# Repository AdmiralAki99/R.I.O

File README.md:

# Smartwatch Software

## Overview

A basic smartwatch software that is used for personal use and understanding how to read schematics, design PCB, understand embedded sytems.

## Render

https://github.com/user-attachments/assets/5ccf8013-91de-4bed-8570-e81a325c24fe

## Schematic

## Features

<ul>
    <li> BLE Communication With Swift Companion App</li>
    <li> Fits Inside 42mm Metal Watch Case </li>
</ul>

## Hardware Used
<ol>
    <li> ESP32 S3 MCU </li>
    <li> GC9A01 TFT Screen 1.28 Touch Screen </li>
    <li> Resistor (160k)</li>
    <li> Resistor (442k)</li>
    <li> 4 pin Magnetic Connector</li>
    <li> JST 2 Pin Connector RA</li>
    <li> Two Vertical Tactile Switch</li>
    <li>Schotky Diode </li>
</ol>

## Challenges Faced

<ul>
    <li> Understanding Schematics to connect the data pins and power pins to the magnetic connector to allow for flashing of the board </li>
    <li> Implementing BLE GATT Server & Characteristics</li>
    <li> Controlling power consumption to increase battery life </li>
    <li> Designing 3D housing for the watch to be placed inside the metal watch</li>
    <li> Designing PCB board using KiCad</li>
</ul>

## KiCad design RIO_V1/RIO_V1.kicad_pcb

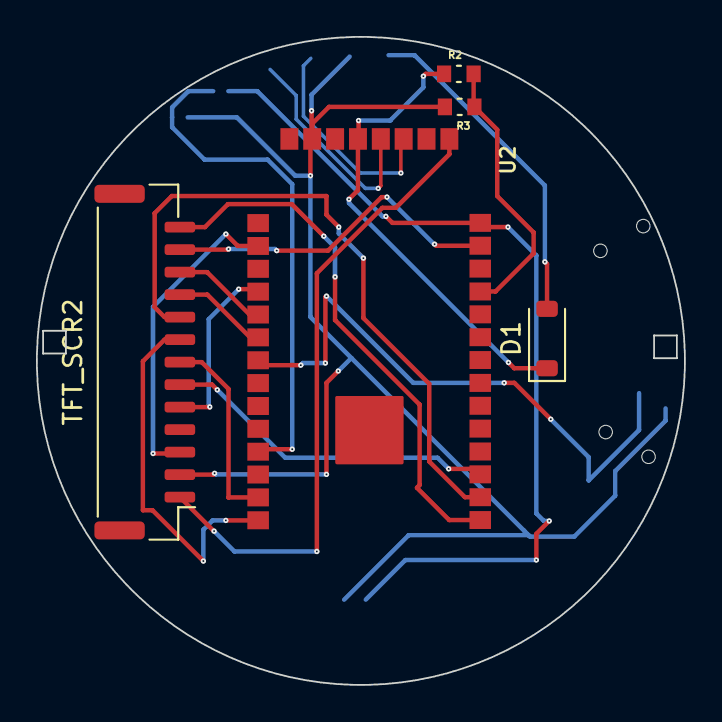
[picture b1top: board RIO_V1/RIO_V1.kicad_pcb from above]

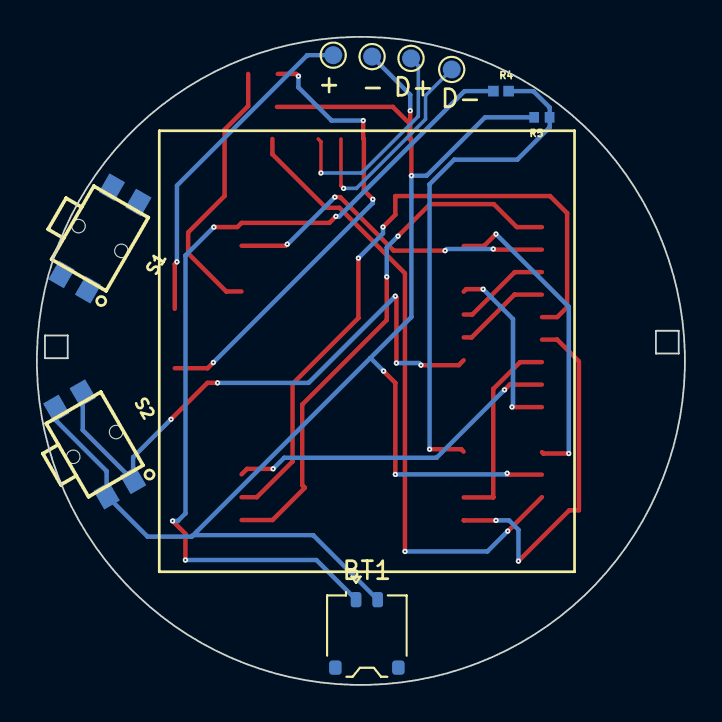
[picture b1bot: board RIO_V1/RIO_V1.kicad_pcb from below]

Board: 2 copper layers, 36.0 x 36.0 mm, 14 parts (9 on the bottom side), 22 nets.

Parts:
+: TestPoint; TestPoint_Pad_D1.0mm
-: TestPoint; TestPoint_Pad_D1.0mm
BT1: Battery; JST_ACH_BM02B-ACHSS-GAN-ETF_1x02-1MP_P1.20mm_Vertical
D1: MBR0530-TP; D_SOD-123
D+: TestPoint; TestPoint_Pad_D1.0mm
D-: TestPoint; TestPoint_Pad_D1.0mm
R2, R3: 50k; RESC1608X55N
R4: 442k; RESC1005X35N
R5: 160k; RESC1005X40N
S1, S2: TL1014BF160QG
TFT_SCR2: GH_CONNECTOR; JST_GH_BM13B-GHS-TBT_1x13-1MP_P1.25mm_Vertical
U2: NanoS3

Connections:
+3V3: TFT_SCR2.1, U2.8 (3v3)
+5V: D1.1 (K), R2.1, U2.4 (5V)
D+: D+.1, U2.6 (D+)
D-: D-.1, U2.5 (D-)
GND: -.1, BT1.2 (-), R3.2, R5.2, S1.1, S1.3, S2.2, S2.4, TFT_SCR2.2, U2.2 (GND)
IO0: S2.1, S2.3, U2.29 (IO0)
IO1: R4.2, R5.1, U2.33 (IO1)
IO3: TFT_SCR2.7, U2.35 (IO3)
IO4: TFT_SCR2.8, U2.36 (IO4)
IO5: TFT_SCR2.13, U2.22 (IO5)
IO6: TFT_SCR2.9, U2.21 (IO6)
IO7: TFT_SCR2.6, U2.20 (IO7)
IO8: TFT_SCR2.10, U2.28 (IO8)
IO9: TFT_SCR2.11, U2.27 (IO9)
IO17: R2.2, R3.1, U2.12 (IO17)
IO21: TFT_SCR2.12, U2.10 (IO21)
IO34: TFT_SCR2.5, U2.26 (IO34)
IO35: TFT_SCR2.4, U2.23 (IO35)
IO37: TFT_SCR2.3, U2.24 (IO37)
unnamed: +.1, D1.2 (A)
RESET: S1.2, S1.4, U2.3 (RESET)
VBAT: BT1.1 (+), R4.1, U2.9 (VBAT)

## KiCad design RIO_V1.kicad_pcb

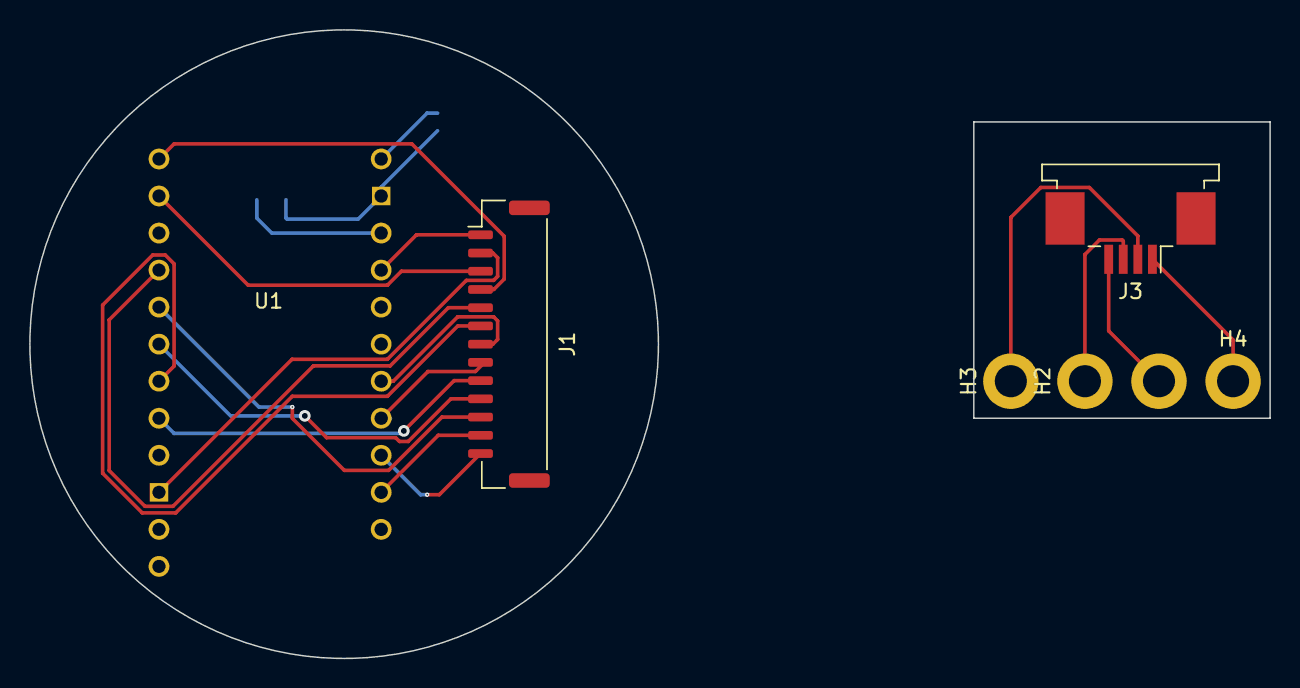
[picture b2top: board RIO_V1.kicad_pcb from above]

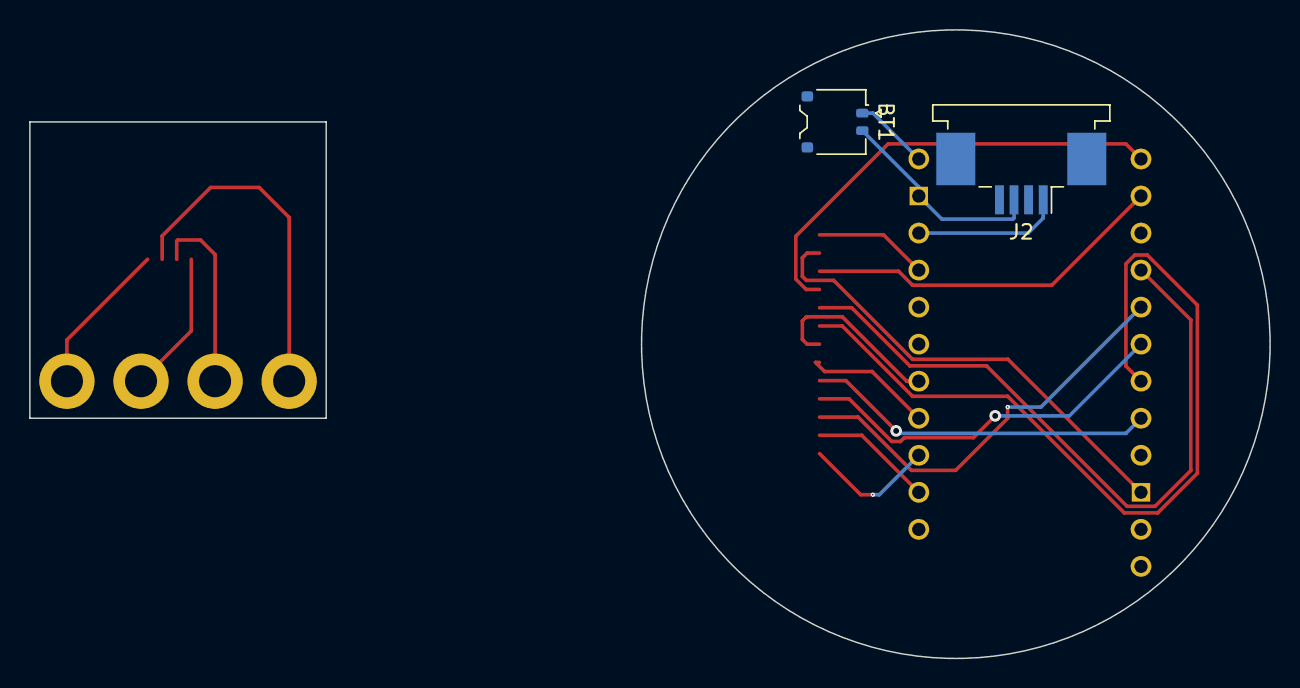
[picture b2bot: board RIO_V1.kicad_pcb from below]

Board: 2 copper layers, 85.1 x 43.1 mm, 9 parts (2 on the bottom side), 20 nets.

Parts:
BT1: Battery; JST_ACH_BM02B-ACHSS-GAN-ETF_1x02-1MP_P1.20mm_Vertical
H1: Pin_2; MountingHole_2.2mm_M2_DIN965_Pad
H2: Pin_3; MountingHole_2.2mm_M2_DIN965_Pad
H3, H4: Pin_4; MountingHole_2.2mm_M2_DIN965_Pad
J1: Conn_01x13_Pin; JST_GH_BM13B-GHS-TBT_1x13-1MP_P1.25mm_Vertical
J2: Conn_01x03_Pin; TE_84952-4_1x04-1MP_P1.0mm_Horizontal
J3: Conn_01x04_Pin; TE_84952-4_1x04-1MP_P1.0mm_Horizontal
U1: TinyS3_Symbol; TinyS3

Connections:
unnamed: BT1.1 (+), U1.1 (VBAT)
unnamed: BT1.2 (-), J2.3, U1.2 (GND)
unnamed: J1.1, U1.4 (3V3)
unnamed: J1.2, U1.14 (GND)
unnamed: J1.3, U1.22 (IO37)
unnamed: J1.4, U1.23 (IO35)
unnamed: J1.5, U1.20 (IO34)
unnamed: J1.6, U1.17 (IO7)
unnamed: J1.7, U1.7 (IO3)
unnamed: J1.8, U1.8 (IO4)
unnamed: J1.9, U1.16 (IO6)
unnamed: J1.10, U1.18 (IO8)
unnamed: J1.11, U1.19 (IO9)
unnamed: J1.12, U1.10 (IO21)
unnamed: J1.13, U1.9 (IO5)
unnamed: J2.1, U1.3 (5V)
unnamed: H4.1, J3.1
unnamed: H3.1, J3.2
unnamed: H2.1, J3.3
unnamed: H1.1, J3.4

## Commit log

2023-09-19 Created Inital Repository
2023-09-19 Created Readme File
    Created Readme file for repo
2023-09-19 Trying Different Menu Styles
    Trying different menu styles to get smooth refresh rate for the main menu
2023-09-19 Changed Analog Watch Face
    Removed minor arcs that from the watch face
2023-09-19 Fixed Bug
    Removed bug that stopped interaction
2023-09-19 Trying different Event Callback
    Trying to figure out Long press callback
2023-09-19 Added Different Menu
    Added Different Menu that is more smooth in the scrolling animation.
2023-09-19 Updated Binaries from PlatformIO
    Updated Binaries need to remove directory from Github
2023-09-23 Code Cleanup
    Code cleanup for some of the files
2023-09-23 Created a Config file to store settings values
    Created a Config file to potentially store the settings values for the smartwatch
2023-09-23 Added Hold Gesture to Create Main Menu
    Added hold gesture to open the menu instead of a click for better ease of use
2023-09-23 Added Define for Analog and Digital Watch Face
    Added a definition that needs to be more dynamic
2023-09-23 Added Watch Face Type Preprocessor Macros
    Added Analog and Digital Watch Face Partition
2023-09-24 Code Cleanup
    Organized the code into cleaner sections that can be debugged easier and more features can be added later
2023-09-24 Need to change BLE Music Metadata Retreival
    Need to change the way music metadata is not cleared from memory
2023-09-24 Added Method to Signal State of Music Playback
    Added simple method to send music playback to device to indicate if track needs to be skipped or rewinded. Need to create method to encode message and decode encoded messages
2023-09-25 Added Method Documentation
    Added method documentation for parsecs.h for better code readability and changed of sendMessage function
2023-09-25 Added Minor Docs
    Added file header to allow for easier checkpoint backup
2023-09-25 Added Minor Docs
    Added Minor docs for each separate screen for easier checkpoint restores
2023-09-25 Trying UML Diagram
    Trying making UML Diagram in VS Code
2023-09-25 Added Initial UML Diagram
    Created Initial Diagram of v0.3 of the smartwatch, need to add variables, functions and also exporting it to format to embed into documentation.
2023-09-26 Created Video Source enum class
    Created Video Source enum class to track state of playback
2023-09-26 Fixed System Error
    Fixed system error that did not left Touch screen to be drawn
2023-09-26 Minor Refactor to prepare for Video Feed
    Minor refactor in anticipation for developing video streaming
2023-09-27 Able to Open a JPEG file stored as uint8_t
    Able to open converted JPEG files. Need to figure out displaying them on screen
2023-09-27 Created a 200x200 to display frames
    Created a 200x200 canvas to display frames. Size restricted due size of RAM available. Need to try projecting decoded JPEG images
2023-09-27 Minor Changes
    Minor changes to check using TFT_eSPI methods
2023-10-02 Added Function Calls to Send Data Over BLE
    Added function calls to send data over BLE from watch to app.
2023-10-02 Removed and Changed BLE Functionality
    Removed and changed BLE functionality to remove the initial values as well as remove the case where my mistake caused multiple transmissions to App
2023-10-02 Changed Function Calls to Display Metadata
    Changed function calls to change the way the music metadata is displayed on the device and removed the error where music labels were concatenated instead of repalced
2023-10-02 Added Artist Name Parsing and Displaying
    Added artist name parsing from BLE message from TimeCraft Link and displaying the metadata
2023-10-04 Added Functionality To Receive Tasks Over BLE
    Added functionality to add tasks over BLE and display them accordingly. The current limits for the tasks is 20 tasks for now.
2023-10-04 Changed Functionality to Refresh Todo List
    Added functionality to refresh the Todo list instead of joining to it
2023-10-04 Reduced Response Time
    Reduced response time from the Apps side, need to store the states of each task in order to get the current status of the task correctly
2023-10-05 Important: Last Stable Checkpoint
    Added New BLE Callback for Todo State. Will only be able to test entire project instead of components after board is replaced.
2023-10-06 Added Task Status Checking For Checkboxes
    Added task status checking for checkboxes so that the current status of the tasks
2023-10-10 Added Parsing for Todo Status
    Added parsing for todo status so that they can be taken and the tasks can be represented accurately on the UI
2023-11-25 Created Documentation
    Created overview documentation for the smartwatch software
2024-06-19 KiCad Schematics & PCB Design
    KiCad Schematics & PCB Design for the board that will be housed in the casing
2024-06-19 PDF Version of KiCad Schematic For Documentation
    PDF version of KiCad Schematic for documentation to be used for reference going forward and work on adding upgrades to it later
2024-06-22 Updated Schematics & PCB To Incorporate Connector
    Updated Schematic and PVB to incorporate the JST Connector instead of resodering it with a TE FPC connector
2024-06-27 Changed TinyS3 To NanoS3
2024-06-29 Added KiCad Files To Folders
    Added new KiCad Schematics and PCB designs for both the main PCB as well as the magnetic POGO connector PCB in the project
2024-06-30 Added Charging Sense Circuit
    Added charging sense circuit to allow for detecting if the circuit is turned on using an IO pin on the MCU
2024-07-02 Updated Symbols Footrprints and Routing
    Updated the symbols, footprints and the PCB routing to work with the new resistors and ADC circuit
2024-07-03 Changed The FPC Connector To A Smaller Pitch
    Changed the FPC connector on the PCB so that the pitch is reduced and overall footprint is minimized as much as possible
2024-07-08 Added New PCB Conenctors, Routes, Components
    Added new PCB components to reduce the height, changed the traces and adjusted for the battery in the PCB
2025-02-13 Added Main File
    Added main file with the working example of LVGL and Display as per ESP-IDF Repo. Will completely rework and delete
